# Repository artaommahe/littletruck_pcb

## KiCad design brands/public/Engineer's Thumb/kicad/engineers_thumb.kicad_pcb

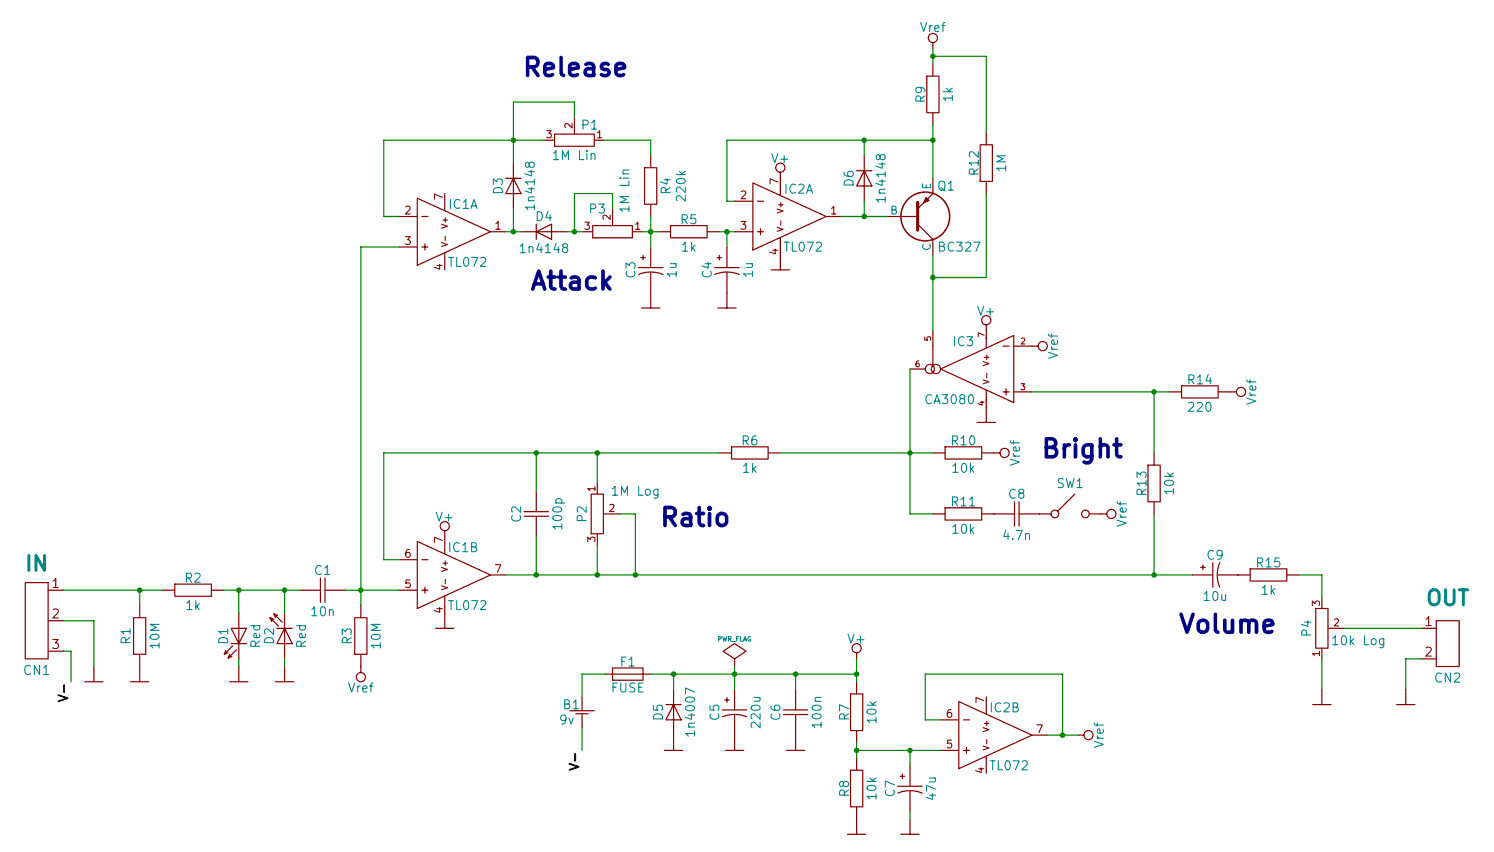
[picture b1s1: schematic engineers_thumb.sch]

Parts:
B1: 9v; socket_power_onboard
C1: 10n; capacitor_5mm_film
C2: 100p; capacitor_5mm_ceramic
C3, C4: 1u; capacitor_2.5mm_electrolytic_5mm
C5: 220u; capacitor_3.5mm_electrolytic_8mm
C6: 100n; capacitor_5mm_ceramic
C7: 47u; capacitor_2.5mm_electrolytic_5mm
C8: 4.7n; capacitor_5mm_film
C9: 10u; capacitor_2.5mm_tantal
CN1: IN; socket_jack_powered-6.35_onboard
CN2: OUT; socket_jack-6.35_onboard
D1, D2: Red; diode_light_2.5mm
D3, D4, D6: 1n4148; diode_5mm
D5: 1n4007; diode_7.5mm
F1: FUSE; fuse_resettable_5mm
IC1, IC2: TL072; opamp_dip8_2.5mm
IC3: CA3080; ic_dip8_2.5mm
P1, P3: 1M Lin; potentiometer_panel_5mm
P2: 1M Log; potentiometer_panel_5mm
P4: 10k Log; potentiometer_panel_5mm
Q1: BC327; transistor_pnp_cbe
R1, R3: 10M; resistor_7.5mm
R2, R5, R6, R9, R15: 1k; resistor_7.5mm
R4: 220k; resistor_7.5mm
R7, R8, R10, R11, R13: 10k; resistor_7.5mm
R12: 1M; resistor_7.5mm
R14: 220; resistor_7.5mm
SW1: SW_ON-OFF_SINGLE; socket_2pin_2.5mm

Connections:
/V-: B1.2, CN1.3
GND: C3.1, C4.1, C5.1, C6.2, C7.1, CN1.2, CN2.2, D1.2, D2.1, D5.1, IC1.4 (V-), IC2.4 (V-), IC3.4 (V-), P4.1, R1.1, R8.2
unnamed: B1.1, F1.2
unnamed: C1.1, D1.1, D2.2, R2.2
unnamed: C1.2, IC1.3 (+), IC1.5 (+), R3.2
unnamed: C2.2, IC1.6 (-), P2.1, R6.1
unnamed: C3.2, P3.1, R4.2, R5.1
unnamed: C4.2, IC2.3 (+), R5.2
unnamed: C7.2, IC2.5 (+), R7.2, R8.1
unnamed: C8.1, R11.2
unnamed: C8.2, SW1.1
unnamed: C9.1, R15.1
unnamed: CN1.1, R1.2, R2.1
unnamed: CN2.1, P4.2
unnamed: D3.1, D4.2, IC1.1
unnamed: D3.2, IC1.2 (-), P1.2, P1.3
unnamed: D4.1, P3.2, P3.3
unnamed: D6.1, IC2.1, Q1.2 (B)
unnamed: D6.2, IC2.2 (-), Q1.3 (E), R9.2
unnamed: IC3.3 (+), R13.1, R14.1
unnamed: IC3.5, Q1.1 (C), R12.1
unnamed: IC3.6, R6.2, R10.1, R11.1
unnamed: P1.1, R4.1
unnamed: P4.3, R15.2

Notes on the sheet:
Ratio
Release
Attack
Bright
Volume

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
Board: 2 copper layers, 44 parts (0 on the bottom side), 26 nets, no tracks yet.

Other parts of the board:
switch_3pdt_stomp_onboard: VAL**; switch_3pdt_stomp_onboard

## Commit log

2014-09-21 initial
2014-09-21 Tech21 Bass Driver
2014-09-26 Earthbound Audio Supercollider
2014-09-27 Earthbound Audio Supercollider, Tech21 Bass Driver
2014-10-02 update gitignore, added kicad libs
2014-10-05 IdiotBox Blower Bass
2014-10-06 Loop Selector w/ 3 leds
2014-10-10 IdiotBox Blower Box
2014-10-10 IdiotBox Blower Box, Loop Selector
2014-10-15 added LTSpice simulation files(asc), Loop Selector
2014-10-15 BOSS CE-5
2014-10-26 BOSS CE-5, Mad Professor Snow White
2014-10-26 added kicad files to gitignore
2014-10-26 Engineer's Thumb compressor, added LED to KiCAD 'drow' lib
2014-10-27 Engineer's Thumb, added LM13700 to KiCAD 'drow' lib
2014-10-28 Engineer's Thumb
2014-11-02 added SLayer6 makros files to .gitignore and repo, removed Engineer's Thumb pdf Schematic
2014-11-03 Small active splitter(AMZ Jfet Splitter), Blackout Effectors Musket fix
2014-11-14 Engineer's Thumb schemetic, KiCAD libs cleanup, added CA3080
2014-11-16 added KiCAD footprints to .gitignore
2014-11-26 more KiCAD footprints
2014-11-26 clean up KiCAD footprints, added opamp dip8, 6.35-jack socket footprints
2014-11-27 added net/cmp to gitignore exclude, added power socket, 3pdt stomp switch KiCAD footprints
2014-11-30 added pnp transistor KiCAD footprint, added pcb file
2014-12-03 Engineer's Thumb pcb
2014-12-12 Engineer's Thumb, added 3PDT switch to KiCAD lib
2014-12-15 added Green Citrus schematic image
2014-12-16 Green Citrus: added KiCAD project/schematic, changed schematic file image
2014-12-17 Green Citrus layout
2014-12-20 Green Citrus
2014-12-22 Green Citrus, added ltspice emulation
2015-01-11 Bass Driver cleanup
2015-01-11 IdiotBox Blower Box tembroblock fixes
2015-01-11 Engineer's Thumb layout, added CA3080, PNP CBE transistor SLayer makroses
2015-01-21 Blower Box, Engineer's Thumb
2015-01-24 Added new parametric eq schematic emulation, added SLayout makroses for onboard power and stomp switch with flat pins
2015-01-30 Update OKKO Diablo Emulation, added KiCAD project
2015-01-31 OKKO Diablo schematic correction, added booster emulation
2015-01-31 added Catalinbread Galileo schematic image and booster emulation
2015-02-06 OKKO Diablo schematic
2015-02-06 OKKO Diablo schematic correction
2015-02-06 fixed KiCAD drow.lib
2015-02-06 OKKO Diablo+ new layout starting
2015-02-07 OKKO Diablo layout in work
2015-02-13 Shin-Ei Fy-2 Fuzzmaster KiCAD schematic, emulation, png schematic file
2015-02-15 Shin-Ei Fy-2 added booster to schematic/emulation
2015-02-15 Shin-Ei Fy-2 layout
2015-02-16 OKKO Diablo
2015-02-17 TrueVal WildScreamer
2015-03-04 fixes
2015-03-05 FX Blender KiCAD schematic
2015-03-05 FX Blender Mini layout
2015-03-10 FX Blender Mini
2015-04-14 added Catalinbread Sabra Cadabra kicad schematic
2015-04-20 Catalinbread Sabra Cadabra. Fixed KiCAD schematic, added png chematic, added slayout
2015-05-03 Tri-Vibe fixes
2015-05-03 added TrueVal's JTM-45 Soundmaker schematic
2015-05-13 WildScreamer fix
2015-07-04 Added Lionsound 14 schematic
2015-07-15 added TrueVal's Archaic Rock Machine dist, Ject Tocker schematics
2015-07-23 added Roger Mayer Octavia schematic and layout
2015-07-24 Roger MayerOctavia layout workaround
2015-07-24 Roger Mayer Octavia layout workaround
2015-07-24 Catalinbread Sabbra Cadabra layout workaround
2015-07-24 Catalinbread Sabbra Cadabra layout workaround, added emulation
2015-07-25 Roger Mayer Octavia, Catalinbread Sabbra Cadabra layouts fixes
2015-08-01 added Basic Audio Scarab Deluxe schematic
2015-08-01 Catalinbread Sabbra Cadabra, Roger Mayer Octavia fixes, added emulation for Octavia
2015-08-08 Tech21 Character Series layout fixes
2015-08-14 Foxx Tone Machine layout fixes
2015-12-29 *. fixes
2016-07-07 mini blender fixes, added png/jpg images to repo
2016-07-07 Tech21 Bass Driver. fixes
2016-08-21 Added JFET Bass Preamp w/ eq emulation and layout
2016-08-21 fixes, added Mooer Solo schematic
2016-08-25 JFET bass preamp fixes
